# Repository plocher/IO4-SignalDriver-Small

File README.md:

# IO4-SignalDriver-Small
## License: CERN Open Hardware Licence v1.2

IO4 Output adapter driver for a 2-head signal mast

Takes an IO4-Output and drives 2x 3-LED common Anode signal heads using a demultiplexor logic chip.

Designed in conjunction with Jay Beckham for his South Shore Lines layout

Circuit info:
  * The board is driven from an IO4 port that carries +5, GND and 4x output signals.
  * Signal heads / LEDs are "common anode" - pin4 of the signal head connector is VCC, the "colors" pins are driven LOW to energize the LED.
  * The board can drive 2x signal heads, each with R, Y, G and DARK aspects
      * Control signals 1 & 2 and  3 & 4, each control one head:
          : 00 - Green
          : 01 - Yellow
          : 10 - Red
          : 11 - Dark
  * This board does not have provision for adjustable LED brightness.  The resistors are fixed at production time for high efficiency LEDS used in SPCoast's Simple Signal masts.

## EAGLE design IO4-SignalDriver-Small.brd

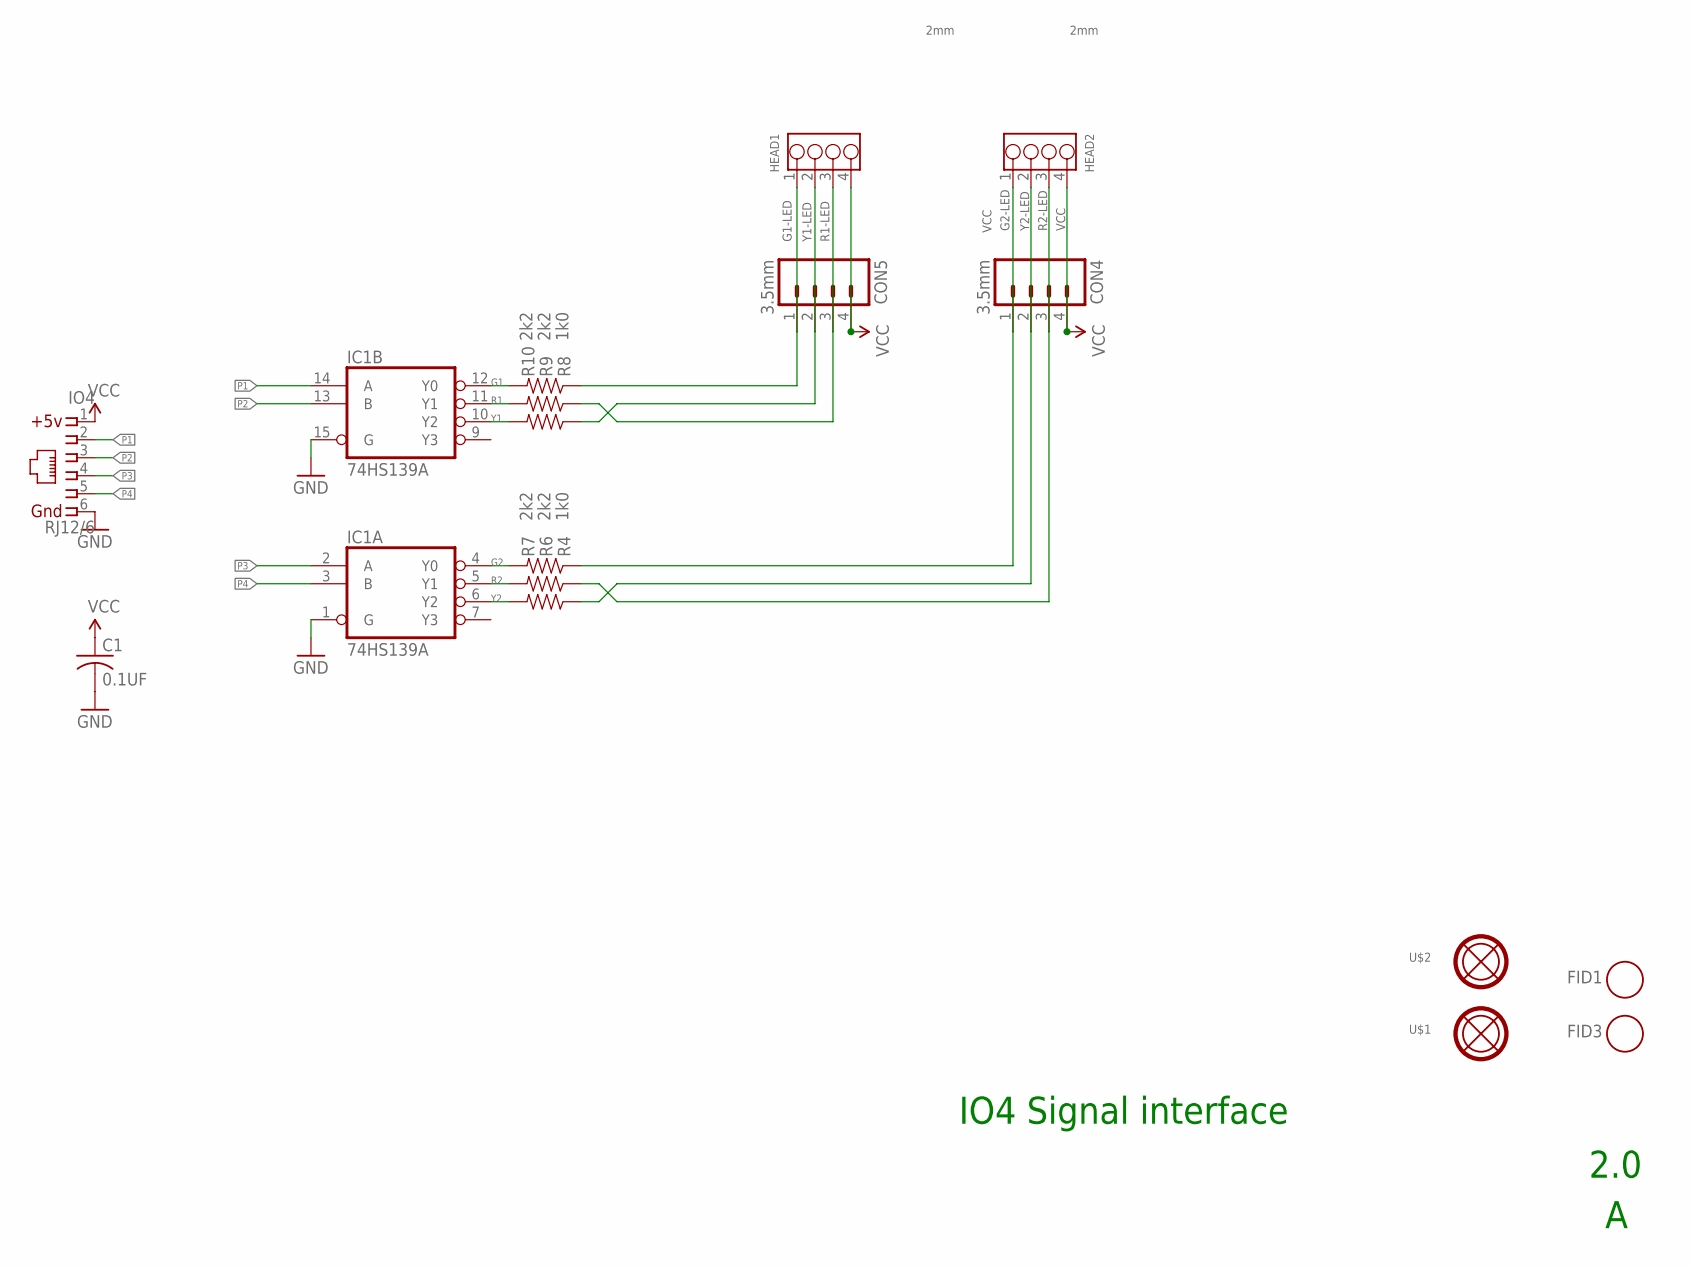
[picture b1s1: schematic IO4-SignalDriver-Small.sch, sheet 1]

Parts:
C1: 0.1UF; 0603-CAP
CON4, CON5: 3.5mm; SCREWTERMINAL-3.5MM-4
FID1, FID3: FIDUCIAL; FIDUCIAL_1MM
HEAD1, HEAD2: 2mm; 4P-2.0
IC1: 74HS139A; SO16
IO4: RJ12/6; RJ25-INVERTED
R4, R8: 1k0; 0603-RES
R6, R7, R9, R10: 2k2; 0603-RES
U$1, U$2: MOUNTINGHOLE

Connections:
G1: IC1.12 (Y0), R10.2
G1-LED: CON5.1, HEAD1.1, R10.1
G2: IC1.4 (Y0), R7.2
G2-LED: CON4.1, HEAD2.1, R7.1
GND: C1.2, IC1.1 (G), IC1.8 (GND), IC1.15 (G), IO4.6
P1: IC1.14 (A), IO4.2
P2: IC1.13 (B), IO4.3
P3: IC1.2 (A), IO4.4
P4: IC1.3 (B), IO4.5
R1: IC1.11 (Y1), R9.2
R1-LED: CON5.3, HEAD1.3, R9.1
R2: IC1.5 (Y1), R6.2
R2-LED: CON4.3, HEAD2.3, R6.1
VCC: C1.1, CON4.4, CON5.4, HEAD1.4, HEAD2.4, IC1.16 (VCC), IO4.1
Y1: IC1.10 (Y2), R8.2
Y1-LED: CON5.2, HEAD1.2, R8.1
Y2: IC1.6 (Y2), R4.2
Y2-LED: CON4.2, HEAD2.2, R4.1

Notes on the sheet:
IO4 Signal interface
2.0

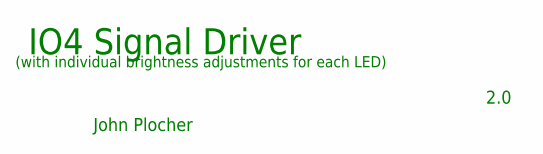
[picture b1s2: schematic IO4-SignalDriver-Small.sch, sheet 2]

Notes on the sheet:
(with individual brightness adjustments for each LED)
John Plocher
2.0
IO4 Signal Driver

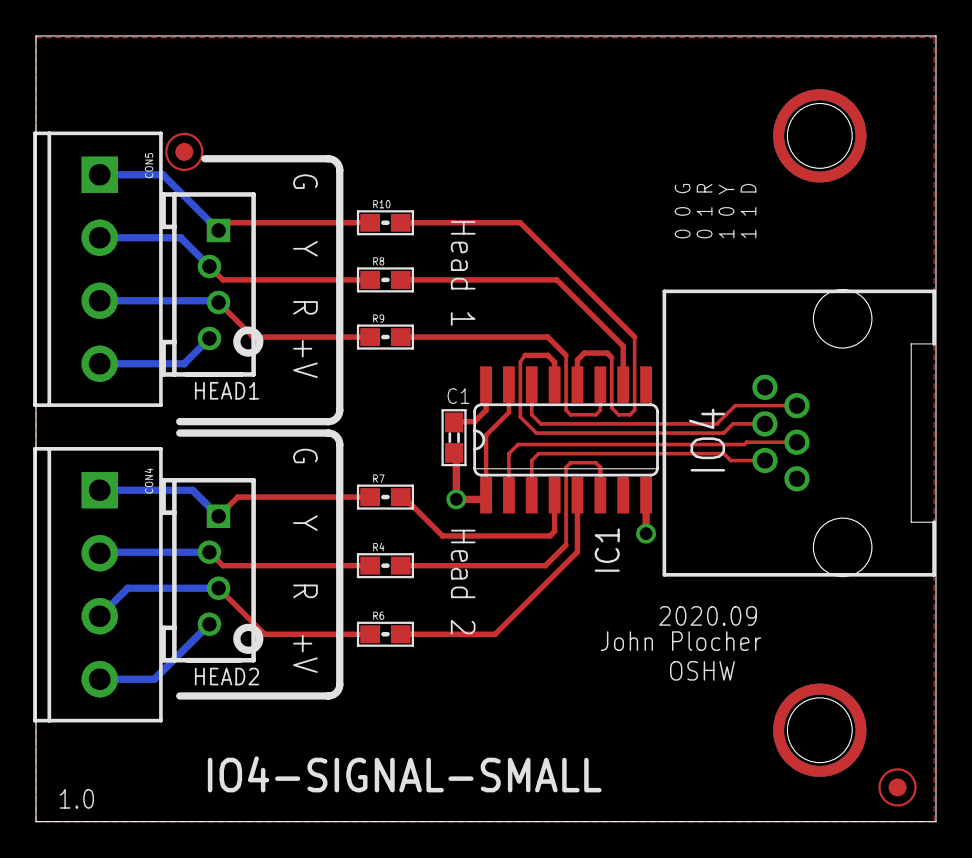
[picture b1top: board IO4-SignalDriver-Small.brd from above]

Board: 2 copper layers, 50.0 x 43.6 mm, 17 parts (0 on the bottom side), 18 nets.

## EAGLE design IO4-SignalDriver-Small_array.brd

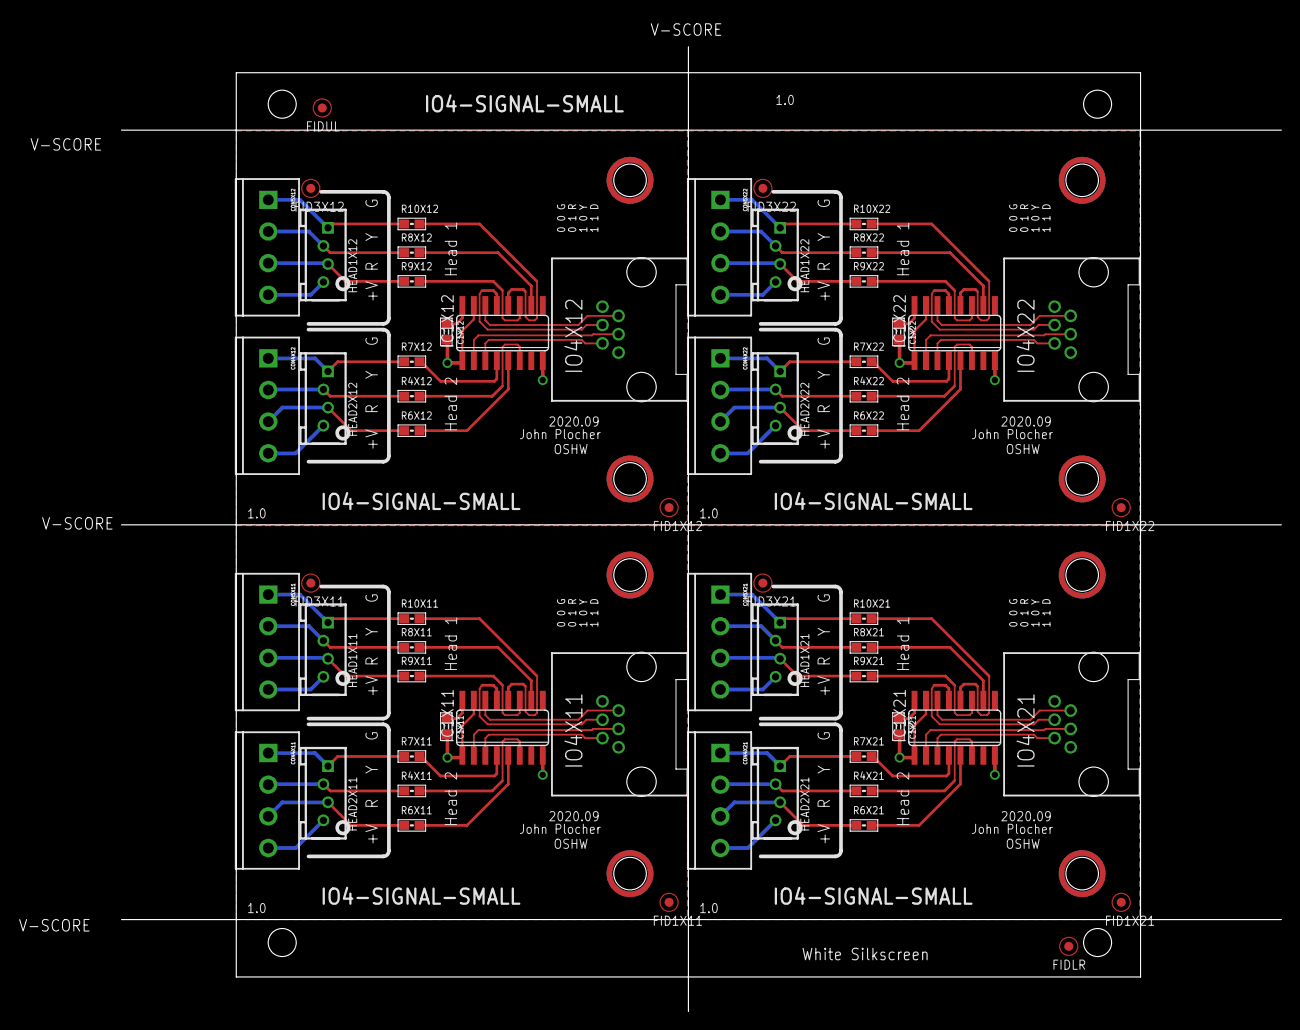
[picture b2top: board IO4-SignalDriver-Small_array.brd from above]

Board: 2 copper layers, 139.6 x 109.8 mm, 71 parts (0 on the bottom side), 72 nets.

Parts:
BOARD: BOARD; BOARD-10X10-2X2-PANEL
C1X11, C1X12, C1X21, C1X22: 0.1UF; 0603-CAP
CON4X11, CON4X12, CON4X21, CON4X22, CON5X11, CON5X12, CON5X21, CON5X22: 3.5mm; SCREWTERMINAL-3.5MM-4
FID1X11, FID1X12, FID1X21, FID1X22, FID3X11, FID3X12, FID3X21, FID3X22: FIDUCIAL; FIDUCIAL_1MM
FIDLR: FIDUCIAL; FIDUCIAL_1MM
FIDUL: FIDUCIAL; FIDUCIAL_1MM
HEAD1X11, HEAD1X12, HEAD1X21, HEAD2X11, HEAD2X21: 2mm; 4P-2.0
HEAD1X22: Head 1; 4P-2.0
HEAD2X12, HEAD2X22: Head 2; 4P-2.0
IC1X11, IC1X12, IC1X21, IC1X22: 74HS139A; SO16
IO4X11, IO4X12, IO4X21, IO4X22: RJ12/6; RJ25-INVERTED
R4X11, R4X12, R4X21, R4X22, R8X11, R8X12, R8X21, R8X22: 1k0; 0603-RES
R6X11, R6X12, R6X21, R6X22, R7X11, R7X12, R7X21, R7X22, R9X11, R9X12, R9X21, R9X22, R10X11, R10X12, R10X21, R10X22: 2k2; 0603-RES
U$1X11, U$1X12, U$1X21, U$1X22, U$2X11, U$2X12, U$2X21, U$2X22: MOUNTINGHOLE

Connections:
G1-LEDX11: CON5X11.1, HEAD1X11.1, R10X11.1
G1-LEDX12: CON5X12.1, HEAD1X12.1, R10X12.1
G1-LEDX21: CON5X21.1, HEAD1X21.1, R10X21.1
G1-LEDX22: CON5X22.1, HEAD1X22.1, R10X22.1
G1X11: IC1X11.12, R10X11.2
G1X12: IC1X12.12, R10X12.2
G1X21: IC1X21.12, R10X21.2
G1X22: IC1X22.12, R10X22.2
G2-LEDX11: CON4X11.1, HEAD2X11.1, R7X11.1
G2-LEDX12: CON4X12.1, HEAD2X12.1, R7X12.1
G2-LEDX21: CON4X21.1, HEAD2X21.1, R7X21.1
G2-LEDX22: CON4X22.1, HEAD2X22.1, R7X22.1
G2X11: IC1X11.4, R7X11.2
G2X12: IC1X12.4, R7X12.2
G2X21: IC1X21.4, R7X21.2
G2X22: IC1X22.4, R7X22.2
GNDX11: C1X11.2, IC1X11.1, IC1X11.8, IC1X11.15, IO4X11.6
GNDX12: C1X12.2, IC1X12.1, IC1X12.8, IC1X12.15, IO4X12.6
GNDX21: C1X21.2, IC1X21.1, IC1X21.8, IC1X21.15, IO4X21.6
GNDX22: C1X22.2, IC1X22.1, IC1X22.8, IC1X22.15, IO4X22.6
P1X11: IC1X11.14, IO4X11.2
P1X12: IC1X12.14, IO4X12.2
P1X21: IC1X21.14, IO4X21.2
P1X22: IC1X22.14, IO4X22.2
P2X11: IC1X11.13, IO4X11.3
P2X12: IC1X12.13, IO4X12.3
P2X21: IC1X21.13, IO4X21.3
P2X22: IC1X22.13, IO4X22.3
P3X11: IC1X11.2, IO4X11.4
P3X12: IC1X12.2, IO4X12.4
P3X21: IC1X21.2, IO4X21.4
P3X22: IC1X22.2, IO4X22.4
P4X11: IC1X11.3, IO4X11.5
P4X12: IC1X12.3, IO4X12.5
P4X21: IC1X21.3, IO4X21.5
P4X22: IC1X22.3, IO4X22.5
R1-LEDX11: CON5X11.3, HEAD1X11.3, R9X11.1
R1-LEDX12: CON5X12.3, HEAD1X12.3, R9X12.1
R1-LEDX21: CON5X21.3, HEAD1X21.3, R9X21.1
R1-LEDX22: CON5X22.3, HEAD1X22.3, R9X22.1
R1X11: IC1X11.11, R9X11.2
R1X12: IC1X12.11, R9X12.2
R1X21: IC1X21.11, R9X21.2
R1X22: IC1X22.11, R9X22.2
R2-LEDX11: CON4X11.3, HEAD2X11.3, R6X11.1
R2-LEDX12: CON4X12.3, HEAD2X12.3, R6X12.1
R2-LEDX21: CON4X21.3, HEAD2X21.3, R6X21.1
R2-LEDX22: CON4X22.3, HEAD2X22.3, R6X22.1
R2X11: IC1X11.5, R6X11.2
R2X12: IC1X12.5, R6X12.2
R2X21: IC1X21.5, R6X21.2
R2X22: IC1X22.5, R6X22.2
VCCX11: C1X11.1, CON4X11.4, CON5X11.4, HEAD1X11.4, HEAD2X11.4, IC1X11.16, IO4X11.1
VCCX12: C1X12.1, CON4X12.4, CON5X12.4, HEAD1X12.4, HEAD2X12.4, IC1X12.16, IO4X12.1
VCCX21: C1X21.1, CON4X21.4, CON5X21.4, HEAD1X21.4, HEAD2X21.4, IC1X21.16, IO4X21.1
VCCX22: C1X22.1, CON4X22.4, CON5X22.4, HEAD1X22.4, HEAD2X22.4, IC1X22.16, IO4X22.1
Y1-LEDX11: CON5X11.2, HEAD1X11.2, R8X11.1
Y1-LEDX12: CON5X12.2, HEAD1X12.2, R8X12.1
Y1-LEDX21: CON5X21.2, HEAD1X21.2, R8X21.1
Y1-LEDX22: CON5X22.2, HEAD1X22.2, R8X22.1
Y1X11: IC1X11.10, R8X11.2
Y1X12: IC1X12.10, R8X12.2
Y1X21: IC1X21.10, R8X21.2
Y1X22: IC1X22.10, R8X22.2
Y2-LEDX11: CON4X11.2, HEAD2X11.2, R4X11.1
Y2-LEDX12: CON4X12.2, HEAD2X12.2, R4X12.1
Y2-LEDX21: CON4X21.2, HEAD2X21.2, R4X21.1
Y2-LEDX22: CON4X22.2, HEAD2X22.2, R4X22.1
Y2X11: IC1X11.6, R4X11.2
Y2X12: IC1X12.6, R4X12.2
Y2X21: IC1X21.6, R4X21.2
Y2X22: IC1X22.6, R4X22.2

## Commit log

2020-09-18 Initial version
2020-09-18 renamed
2020-10-05 added values for connectors
2020-10-06 normalized values
